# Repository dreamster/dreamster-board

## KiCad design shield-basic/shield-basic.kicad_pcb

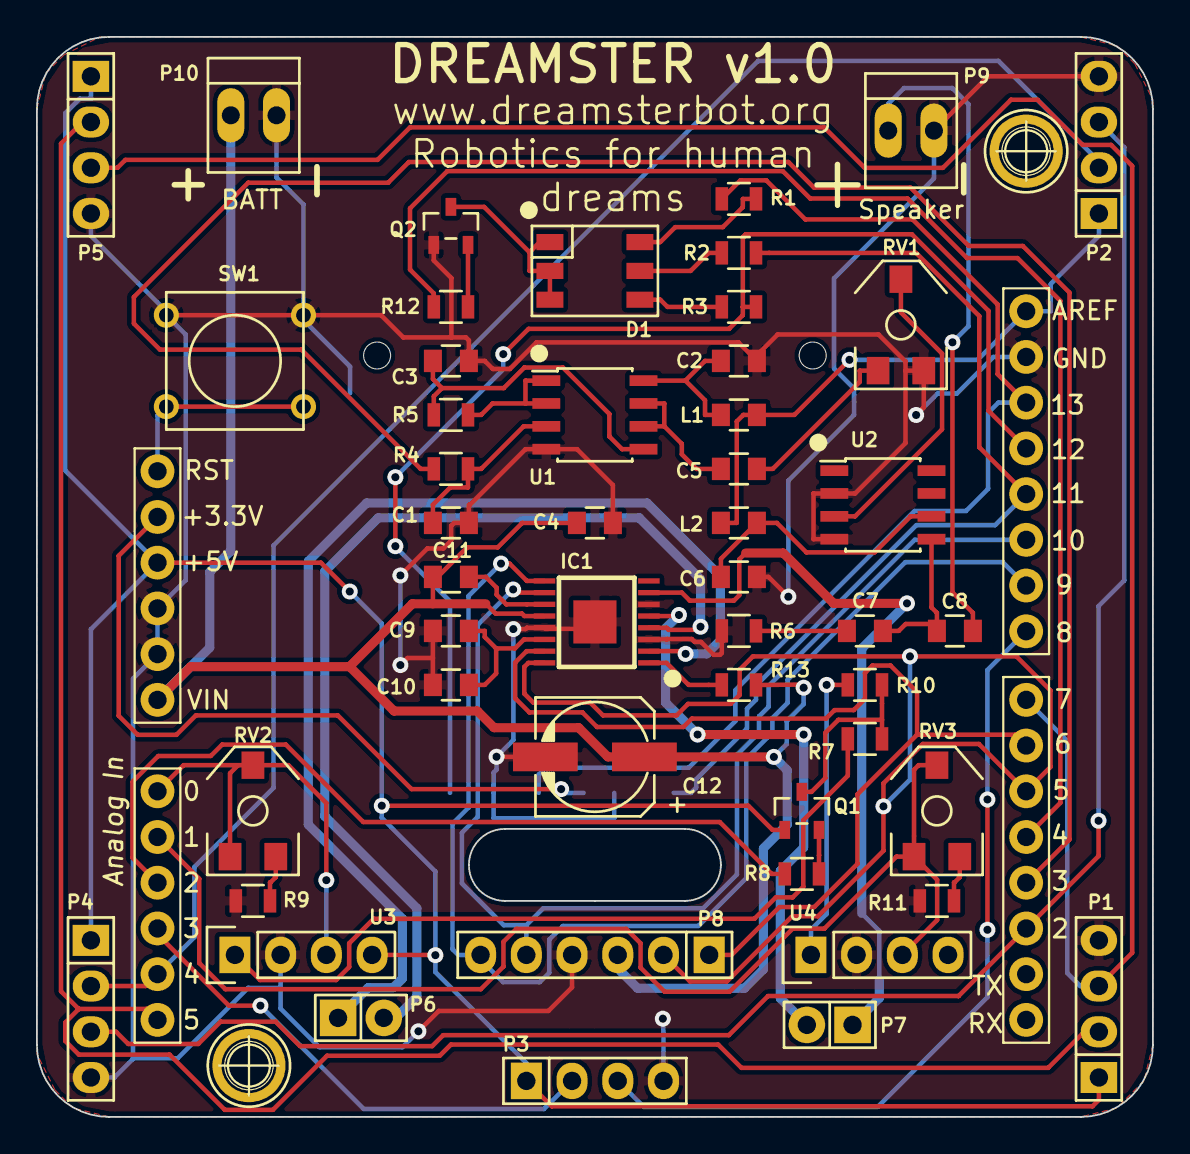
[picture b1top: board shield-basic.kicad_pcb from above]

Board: 2 copper layers, 62.0 x 60.0 mm, 53 parts (1 on the bottom side), 52 nets.

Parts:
C1, C3: 18n; C_0805
C2, C6: 100 nF; C_0805
C4, C9: 100n; C_0805
C5: 3.3 uF; C_0805
C7: 47n; C_0805
C8: 10 uF; C_0805
C10: 2.2u; C_0805
C11: 10n; C_0805
C12: 220u; c_elec_6.3x7.7
CON1: SD_Card; SD_Card_Receptacle
D1: LED_RGB_A; rgb_led_plcc6
IC1: DRV8833; drv8833
L1, L2: 1 uH; C_0805
P1, P2, P3, P4, P5: CONN_01X04; Socket_Strip_Straight_1x04
P6, P7: CONN_01X02; Socket_Strip_Straight_1x02
P8: CONN_01X06; Socket_Strip_Straight_1x06
P9: Speaker; PINHEAD1-2
P10: CONN_01X02; PINHEAD1-2
P11, P12: CONN_01X01; 1pin
Q1: BC857; sot23
Q2: BC847; sot23
R1, R2, R3, R12: 10k; R_0805
R4, R5: 2.2k; R_0805
R6: 10; R_0805
R7, R8, R9, R10, R11: 100; R_0805
R13: 47k; R_0805
RV1, RV2, RV3: 10k; POT_SMD
SW1: SW_PUSH; SW_PUSH_SMALL
U1: TL082; SOIC-8_3.9x4.9mm_Pitch1.27mm
U2: LM386; SOIC-8_3.9x4.9mm_Pitch1.27mm
U3, U4: TCRT1000; Socket_Strip_Straight_1x04
U5: ARDUINO_SHIELD; arduino_shield

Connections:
+3V3: CON1.4, U5.3.3V
+5VD: L1.1, L2.1, P1.1, P2.1, P3.1, P4.1, P5.1, Q1.1, U3.4, U4.4, U5.5V, U5.AREF
+BATT: C4.1, C11.2, C12.1, IC1.12, P8.3, P10.1, R13.1, U5.VIN
/BLUE: CON1.5, R1.1, U5.D13
/ECHO_A: P3.3, U5.D8
/ECHO_B: P2.3, P4.3, U5.D2
/ECHO_C: P1.3, P5.3, U5.D7
/GREEN: CON1.2, R2.1, U5.D11
/LED_enable: R12.1, U5.D4
/RED: CON1.7, R3.1, U5.D12
/RESET: SW1.1, U5.RES
/TRG_A: P3.2, U5.A3
/TRG_B: P2.2, P4.2, U5.A4
/TRG_C: P1.2, P5.2, U5.A5
/hbridge/LM+: IC1.7, P7.1
/hbridge/LM-: IC1.5, P7.2
/hbridge/LMI1: IC1.9, P8.6, U5.D9
/hbridge/LMI2: IC1.10, P8.5, U5.D10
/hbridge/RM+: IC1.2, P6.1
/hbridge/RM-: IC1.4, P6.2
/hbridge/RMI1: IC1.16, P8.2, U5.D5
/hbridge/RMI2: IC1.15, P8.1, U5.D6
/irsensor/LSENS: RV2.1, RV2.2, U3.3, U5.A0
/irsensor/RSENS: RV3.1, RV3.2, U4.3, U5.A1
/irsensor/~EMITTER: R8.2, U5.A2
/sound/In: R4.2, U5.D3
GND: C1.2, C2.2, C3.2, C4.2, C6.2, C9.2, C10.2, C12.2, CON1.3, CON1.6, CON1.12, CON1.13, IC1.3, IC1.6, IC1.13, P1.4, P2.4, P3.4, P4.4, P5.4, P8.4, P9.2, P10.2, Q2.1, R6.2, R9.2, R11.2, RV1.3, SW1.2, U1.4, U2.2, U2.4, U3.2, U4.2, U5.GND@
unnamed: C1.1, R4.1, U1.3
unnamed: C2.1, L1.2, U1.8
unnamed: C3.1, R5.1, U1.5
unnamed: C5.1, U1.6, U1.7
unnamed: C5.2, RV1.1
unnamed: C6.1, L2.2, U2.6
unnamed: C7.1, C8.1, U2.5
unnamed: C7.2, R6.1
unnamed: C8.2, P9.1
unnamed: C9.1, C10.1, IC1.14
unnamed: C11.1, IC1.11
unnamed: D1.1, D1.2, D1.3, Q2.3
unnamed: D1.4, R3.2
unnamed: D1.5, R2.2
unnamed: D1.6, R1.2
unnamed: IC1.1, R13.2
unnamed: Q1.2, R8.1
unnamed: Q1.3, R7.1, R10.1
unnamed: Q2.2, R12.2
unnamed: R5.2, U1.1, U1.2
unnamed: R7.2, U3.1
unnamed: R9.1, RV2.3
unnamed: R10.2, U4.1
unnamed: R11.1, RV3.3
unnamed: RV1.2, U2.3

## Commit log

2014-10-10 Initial commit, some spec defined.
2014-11-22 Add USB and Power schematics taken from ArduinoUno
    These are taken from the Kicad version of the Arduino Uno rev3 project.
2015-01-26 first version of dreamster-shield (work in progress)
2015-02-14 Added sound and completed irsensor
2015-02-14 Removed unused libraries from kicad project
2015-02-16 Organizo el puente h y agrego la sd. faltaria comfirmar que la asignacion de pines es adecuada y que no falten componentes. Se puede empezar con el pcb
2015-02-20 shield-basic schematics almost finished. starting pcb
2015-02-22 update on cmp
2015-02-22 updated on schematics and footprints
2015-02-22 Place the components in the Board. Change some footprint because kicad will remove the library.
2015-02-22 Change the board size
2015-02-22 Added reset buttom.
2015-02-22 Correct HCS04 sensor position.
2015-02-22 Correct LED RGB position.
2015-02-22 PCB routed.
2015-02-22 Added BOM.
2015-02-23 fix some issues on schematic
2015-02-23 The board is routed again, to fix some problems.
2015-02-24 Fix: #6 Add Gnd Plane. Fix: #9 Change IR footprint. Fix: #10 Move the trimmer, the orientation is ok.
2015-02-24 finished h-bridge and updated some values
2015-02-24 Added footprint for R13
2015-02-24 Fix #7: The connector was move to the board edge. Fix #8: Added a hole for the wires. Fix #11: The board now is bigger to get the at the proper distance. Fix: #12: Now the LED won't be covered by the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
2015-02-24 Change the slogan in the board.
2015-02-25 Fix #13: The capacitor was moved next to the IC Fix #14: I added both simbols Fix #15: I add power pad. Fix #16
2015-02-26 Fixed some minor issues
2015-02-26 fixed some marks and cetered pcb
